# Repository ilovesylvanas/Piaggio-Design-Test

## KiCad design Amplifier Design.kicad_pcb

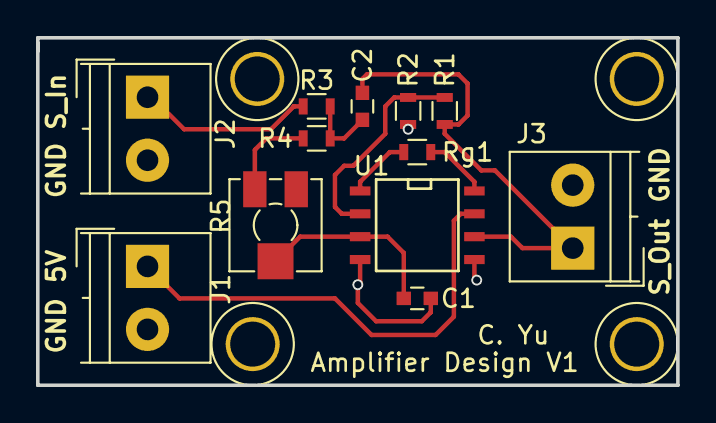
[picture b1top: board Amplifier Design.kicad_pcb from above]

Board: 2 copper layers, 35.6 x 19.3 mm, 12 parts (0 on the bottom side), 10 nets.

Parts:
C1, C2: 1nf; C_0603
J1: Power Input; TerminalBlock_4UCON_19963_02x3.5mm_Straight
J2: Singal Input 3.5mm; TerminalBlock_4UCON_19963_02x3.5mm_Straight
J3: Signal Output; TerminalBlock_4UCON_19963_02x3.5mm_Straight
R1: 30k; R_0603
R2: 20k; R_0603
R3, R4: 10k; R_0603
R5: TS53YJ 50k; Potentiometer_Trimmer_Vishay_TS53YJ
Rg1: 100k; R_0603
U1: AD620; SOIC-8-N

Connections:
+5V: J1.1, U1.7
/S_Input: J2.1, R3.1
/S_Output: C2.2, J3.1, R1.1, U1.6
GND: C1.2, J1.2, J2.2, J3.2, R2.2, U1.4, U1.5
unnamed: C1.1, R5.2, U1.3
unnamed: C2.1, R3.2, R4.1
unnamed: R1.2, R2.1, U1.2
unnamed: R4.2, R5.1
unnamed: Rg1.1, U1.8
unnamed: Rg1.2, U1.1
